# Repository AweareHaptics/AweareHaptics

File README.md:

# AweareHaptics

Nowadays, the french population amounts more than 207 000 blind people and more than a million people suffer from visual defficiencies. According to the OMS, the number of visually impaired people should triple by 2050. Currently, the support tools developed and available for these people are not technologically advanced and often require significant purchase costs. We therefore decided to develop a tool to help with spatial orientation, accessible to all, for the blind or visually impaired.

**Aweare Haptics is an open source project on the development of a haptic vest allowing the blind or visually impaired to orient themselves in their surrounding environment.**

Aweare Haptics is a student project in partnership with the CRI.

This readme is a comprehensive guide on how to use the Git so you can build the vest for yourself. It also contains explainations on our choices so you can adapt it for yourself.

### Requirements

List of hardware required to get started with your project:

- 3D printer
- Soldering station
- Sewing station

# Synopsis

The haptic vest is composed of infrared sensors to detect obstacles, 2 movuinos to transfer instructions to the motor actuators sewn to the vest. The location of the vibrators was determined by performing a sensitivity mapping. 

# Brief

The vest will be entirely made by you. This guide will give you the different components we used to make our own vest. If at any point in the process of building it, you think that something we made isn't adapted for you, don't hesitate to customize it. This repository is mostly a guideline to help you along the way. We will explain our thought process so you can better understand our choices.

The Vest in itself is made in 2 separate parts. Each part is controlled by one movuino board. The first one is the motor control. 

# Architecture of this repository

This repository is divided into multiple folders :

## 3D Model

In this folder you will find two other folders. They include the 3D model that we use to make the vest :

- "Holders" contains the ones used to support the sensors in the vest

- "Caps" contains the ones used to encapsulate the vibration motor.

## Code 

This folder is composed of two folders :
- "Motors" contains the code to upload to the movuino that operates the motors
- "Sensors" contains the code to upload to the movuino that operates the sensors

The code manages the wifi connection. The motor part takes care of setting up the server whereas the sensors represent the hotspot/client.

#  Motor Actuators

## Required hardware

For every motor used you'll need the following components:
- Néomotor PCB: you can find our brd file in the repository
- SMD resistor 10Ω type 0805 : link to [manufacturer reference : CRCW080510R0FKEA](https://fr.rs-online.com/web/p/resistances-cms/6790825/)
- SMD resistor 100Ω type 0805 : link to [manufacturer reference : CR0805-FX-1000ELF](https://fr.rs-online.com/web/p/resistances-cms/7408978/)
- SMD resistor 442Ω type 0805 : link to [manufacturer reference : ERA6AEB4420V](https://fr.rs-online.com/web/p/resistances-cms/7086023/)
- SMD resistor 4KΩ type 0805 : link to [manufacturer reference : CRCW08054K02FKEA](https://fr.rs-online.com/web/p/resistances-cms/6791471/)
- Capacitor type 104 : 10nF, SMD type 0805 :  link to  [manufacturer reference : CC0805KRX7R9BB103](https://fr.rs-online.com/web/p/condensateurs-ceramique-multicouches/4614013/)
- Transitor npn SOT-32 :  link to  [manufacturer reference : MMBT3904LT1G](https://fr.rs-online.com/web/p/transistors-bipolaires-bjt/5450343/)
- Vibration Motor [Type Model NFP-P0716](https://nfpshop.com/product/7mm-vibration-motor-16mm-type-model-nfp-p0716-3v-12000rpm-7-3g-amplitude)

## Setting up the PCB

You'll need to order or make your own PCB with the brd file found on this repository to make the motors work.

## Mounting/Assembly

## Wiring
 - Connect the GND pin of the movuino to the IN GND pin of the pcb
 - Connect the +5V pin of the movuino to the IN +5V pin of the pcb
 - Connect the +3V pin of the movuino to the IN +3V pin of the pcb
 - Connect the D9 pin of the movuino to the IN DIN pin of the pcb
 - Connect the two motor wires to the motor labeled pins on the pcb (in whatever order as the motor isn't polarized)

Then connect :
 - The OUT GND of the first pcb to the following pcb on its IN GND pin
 - The OUT +5V of the first pcb to the following pcb on its IN +5V pin
 - The OUT +3V of the first pcb to the following pcb on its IN +3V pin
 - The DOUT pin of the first pcb to the DIN of the following pcb 

## Code 

Upload the source code to the movuino

The movuino card becomes a sever socket on the address 192.168.4.2
A maximum of one client can connect at a time : this can be changed in the file : ... define BN_CLIENT // TODO ADD NAME OF FILE

The server receives messages from the clients. The messages need to be formated in strings containing the id of the vibration motor that we want to pilot along with its intensity whose value ranges from 0 to 3

## Solder the PCB

The motors PCB are made to all be in series of one another. The first PCB has its 3.3V to the 3 Volts battery. The 5V is connected to the movuino's 5V. Then the DIN is connected to the D4 pin of the movuino. The ground is conected to the shared ground of the movuino and the 3V battery.

For the I/Os of the other PCB, the OUT first board is directly linked to the IN of the second board. The OUT of the second is connected to the IN of the third and continue until all your motor controller are linked. The OUT of the last board doesn't need to be connected anywhere.

For the Motor pins, you just need to connect them to a exentric mass vibration motor. They can be wired in both direction.

For each PCB you also have to solder the resistors, capacitor, transistor and the microcontroller.

### soldering the passive components :

R1 is the 400 Ohms resistor.
R2 is the 4K Ohms resistor.
R3 is the 100 Ohms resistor.
R4 is the 10 Ohms resistor.
C1 is the capacitor.

### soldering the Microcontroller :

To solder the MicroController you have to put the tiny hole such as it is facing you and in the top left. Then you can solder it to the board. 

## Mounting

# Infrared Sensors

## Required hardware

- Prototyping plate : link to [manufacturer reference  : 743635] https://fr.rs-online.com/web/p/cartes-matrices/4853892/
- Infrared sensor VL53L0X TECNOIOT (measures up to 2 meters) : link to [manufacturer reference : A513-VL53L0X-297-5PCS ]
https://www.amazon.fr/TECNOIOT-VL53L0X-Flight-Distance-GY-VL53L0XV2/dp/B084BTP479/ref=sr_1_6?__mk_fr_FR=%C3%85M%C3%85%C5%BD%C3%95%C3%91&crid=6Q645XXPDDA7&dchild=1&keywords=lidar+arduino&qid=1606946373&sprefix=lidar+%2Caps%2C326&sr=8-6
- Infrared sensor VL53L1X STMicroelectronics (measures up to 4 meters): link to [manufacturer reference : VL53L1X-SATEL] https://fr.rs-online.com/web/p/modules-de-developpement-pour-capteurs/1827794/?cm_mmc=FR-PPC-DS3A-_-bing-_-3_FR_FR_Modules+de+d%C3%A9veloppement+pour+capteurs_STMicroelectronics_Exact-_-STMicroelectronics+-+Modules+de+d%C3%A9veloppement+pour+capteurs+-+1827794-_-vl53l1x+satel&matchtype=e&kwd-71743717917902:loc-66&gclid=534000e661d01b55fc8760f1bc5fa77a&gclsrc=3p.ds&msclkid=534000e661d01b55fc8760f1bc5fa77a

## Setting up the prototyping plate

Solder a line for 5V, a line for GND, a line for SCL and a line for SDA.

## Mouting/Assembly

## VLX53L0X pins

### Board description

Take the board with its captor facing you and in the right side of the board. The pins are in the left side. From top to bottom we have :

- Vin 
- Ground
- SCL
- SDA
- GPIO1 (unused for this project)
- XSHUT

## VLX53L1X pins

Schematics for the VL53L1X corresponding pins :

### Schematic description

Take the board with its captor facing you and in the right side of the board. The pins are in the left side. The most bottom left is the INT pin, it is unused for this project. The one above the INT pin is the XSDN pin. Above the XSDN pin is the Vdd pin. Right to Vdd is the ground pin. Below the ground you have the SDA pin. And below SDA is SCL. All other pin are unused.

## Wiring

### Wiring schematic :

### Schematic description

 - Connect the GND pin of the movuino to any line on the prototyping plate which becomes its designated line. (GND)
 - Connect the +3V pin of the movuino to any line on the prototyping plate which becomes its designated line. (+3V)
 - Connect the SCL pin of the movuino to any line on the prototyping plate which becomes its designated line. (SCL)
 - Connect the SDA pin of the movuino to any line on the prototyping plate which becomes its designated line. (SDA)

Connect then for every sensor:

 - Connect the GND pin of the sensor to the desigLnated GND line on the prototyping plate
 - Connect the VIN/VDD pin of the sensor to the designated +3V line on the prototyping plate
 - Connect the SCL pin of the sensor to the designated SCL line on the prototyping plate
 - Connect the SDA pin of the sensor to the designated SDA line on the prototyping plate
 - Connect the pins D3, D4, D5... of the movuino to the XSHUT pin for the sensor VL53L0X or XSDN pin for the VL53L1X sensor.

## Code 

# Sensibility protocole

Sensibility mapping process:

Before getting started with the mapping, you'll need to prepare your work environment.
You'll need to carry out the protocole by using the body proportions of the person wearing the vest.
You'll need to use a vibration motor connected to a power source of 3.3V to map out the sensitive areas of the person's body.

## First step : Divide into squares the person's body

We'll seperate the torso, the back and the arms into different testing areas.

 -On the torso : seperate in 10 different areas
 --Area 1 and 2 : Upper left and right part of the torso 
 --Area 3 and 4 : left and right part of the chest
 --Area 5 and 6 : left and right part of the ribs under the chest area
 --Area 7 and 8 : left and right part of the belly
 --Area 9 and 10 : left and right part of the hips

 -On the back : seperate in 8 different areas.
 --Area 1 and 2 : left and right part of the shoulder blades
 --Area 3 and 4 : left and right part of the ribs under the shoulder blades
 --Area 5 and 6 : left and right part of lower back (lumbar region)
 --Area 7 and 8 : left and right part of hips

 -On the arms : seperate in 4 different areas
 --Area 1 : right shoulder
 --Area 2 : right arm 
 --Area 3 : left shoulder
 --Area 4 : left arm 

## Second step : Mapping out the sensitive areas

- Start by powering up the motor with a voltage of 3.3V.
WARNING : In order for the mapping to be correct, the motor needs to be supplied with a constant voltage of 3.3V for the duration of the tests.

-In order to familiarize yourself with the feeling of the vibrating motor, try out every area at least once before ruling out the ones that are too sensitive.

-Position the motor on every testing area and define one of the following feedback:
--Extremely sensitive area : red
--Sensitive area : orange
--Not very sensitive area : yellow
--Not recommended area (private regions or no sensitivity) : white

-We recommend repeating the protocole multiple times for better results.

# Authors

* [**Guicharnaud Léo**](https://github.com/Lightman31)
* [**Buot Adrien** ](https://github.com/Bubu781 )
* [**terre Mikhali** ](https://github.com/Mikhali)
* [**Sabatey Clara** ](https://github.com/clarasbty)
* [**Noiraux Coline** ](https://github.com/NoireauxColine)
* [**Beurotte Marine** ](https://github.com/mama98)

# Version Francaise :

De nos jours, on compte parmis la population française plus de 207 000 aveugles et plus d’1 million de personnes souffrant de cécité visuelle. De plus, d’après l’OMS, le nombre de malvoyants pourrait trippler d’ici 2050. Actuellement, les outils d’aide développés pour ces personnes sont peu avancés technologiquement et nécessite souvent d’important coût d’achat. Nous avons donc décidé de développer un outil d’aide à l’orientation dans l’espace accessible à tous pour les personnes aveugles et malvoyantes.

**Aweare Haptics est une veste haptique open source permettant aux personnes aveugles et malvoyantes de s’orienter dans leur environnement.**

# Pour commencer

Entrez ici les instructions pour bien débuter avec votre projet...

### Pré-requis

Ce qu'il est requis pour commencer avec votre projet du point de vue du matériel

- Imprimante 3D
- Poste de soudure
- Poste de couture

# Démarrage

Notre veste sera composée de capteurs infrarouge pour détecter la présence d’obstacle et de movuino pour transmettre l’information aux actuateurs présent sur la veste. L’emplacement des vibreurs a été déterminés par la réalisation d’une cartographie de sensibilité.

#  Partie moteurs actuateurs

## Matériel

Pour chaque moteur vous aurez besoin de :

- faire faire un pcb néomotor : le fichier brd est dans le repo
- résistance 10Ω boitier 0805 : lien vers la [référence fabriquant : CRCW080510R0FKEA](https://fr.rs-online.com/web/p/resistances-cms/6790825/)
- résistance 100Ω boitier 0805 : lien vers la [référence fabriquant : CR0805-FX-1000ELF](https://fr.rs-online.com/web/p/resistances-cms/7408978/)
- résistance 442Ω boitier 0805 : lien vers la [référence fabriquant : ERA6AEB4420V](https://fr.rs-online.com/web/p/resistances-cms/7086023/)
- résistance 4KΩ boitier 0805 : lien vers la [référence fabriquant : CRCW08054K02FKEA](https://fr.rs-online.com/web/p/resistances-cms/6791471/)
- Condensateur type 104 : 10nF, boitier 0805 : lien vers la [référence fabriquant : CC0805KRX7R9BB103](https://fr.rs-online.com/web/p/condensateurs-ceramique-multicouches/4614013/)
- transitor npn simple boitier SOT-32 : lien vers la [référence fabriquant : MMBT3904LT1G](https://fr.rs-online.com/web/p/transistors-bipolaires-bjt/5450343/)
- moteur vibrant [Type Model NFP-P0716](https://nfpshop.com/product/7mm-vibration-motor-16mm-type-model-nfp-p0716-3v-12000rpm-7-3g-amplitude)

## Fabrication du pcb

vous aurez besoin de commander ou bien de fabriquer des PCB, pour bien faire fonctionner les moteurs vibrant

## Montage

AJOUTER SCHEMA

## Branchements
 - brancher le GND de la movuino sur le GND du pcb
 - brancher le +5V de la movuino sur le +5V du pcb
 - brancher le +3V de la movuino sur le +3V du pcb
 - brancher la pin D9 de la movuino sur le DIN du pcb
 - brancher les deux fils sur moteur sur le bornes moteur du pcb. (le moteur n'est pas polarisé)

brancher ensuite :
 - le GND du pcb sur le GND du pcb suivant
 - le +5V de pcb sur le +5V du pcb suivant
 - le +3V de pcb sur le +3V du pcb suivant
 - la pin D9 de pcb sur le DIN du pcb suivant

## Code 

téléverser le code source sur la movuino

la carte movuino devient un serveur socket sur l'adresse 192.168.4.2
1 client max peut s'y connecter : ce nombre est modifiable dans le fichier ... : le define BN_CLIENT // TODO : dire le nom du fichier  

le serveur ne fait que recevoir des messages des clients. le message doit etre formaté un string cntenant le numéo de l'actuateur à faire vibrer, ainsi qu'une intensité ayant une valeur comprise entre 0 et 3 

## Souder les PCBd

## Monter..

#  Partie capteurs infrarouge

## Matériel

- Plaque de prototypage : lien vers la [référence fabriquant : 743635] https://fr.rs-online.com/web/p/cartes-matrices/4853892/
- Capteur infrarouge VL53L0X TECNOIOT (mesure jusqu'à 2m) : lien vers la [référence fabriquant : A513-VL53L0X-297-5PCS ]
https://www.amazon.fr/TECNOIOT-VL53L0X-Flight-Distance-GY-VL53L0XV2/dp/B084BTP479/ref=sr_1_6?__mk_fr_FR=%C3%85M%C3%85%C5%BD%C3%95%C3%91&crid=6Q645XXPDDA7&dchild=1&keywords=lidar+arduino&qid=1606946373&sprefix=lidar+%2Caps%2C326&sr=8-6
- Capteur infrarouge VL53L1X STMicroelectronics (mesure jusqu'à 4m): lien vers la [référence fabriquant : VL53L1X-SATEL] https://fr.rs-online.com/web/p/modules-de-developpement-pour-capteurs/1827794/?cm_mmc=FR-PPC-DS3A-_-bing-_-3_FR_FR_Modules+de+d%C3%A9veloppement+pour+capteurs_STMicroelectronics_Exact-_-STMicroelectronics+-+Modules+de+d%C3%A9veloppement+pour+capteurs+-+1827794-_-vl53l1x+satel&matchtype=e&kwd-71743717917902:loc-66&gclid=534000e661d01b55fc8760f1bc5fa77a&gclsrc=3p.ds&msclkid=534000e661d01b55fc8760f1bc5fa77a

## Elaboration de la plaque de prototypage 

METTRE PHOTO DE LA PLAQUE

faire une ligne 5V, une ligne GND, une ligne SCL et une ligne SDA

## Montage

Schema des pins du VL53L1X :

## Branchements

 - brancher le GND de la movuino sur une ligne de la plaque 
 - brancher le +3V de la movuino sur une ligne de la plaque 
 - brancher la pin SCL de la movuino sur une ligne de la plaque
 - brancher la pin SDA de la movuino sur une ligne de la plaque

brancher ensuite pour chaque capteurs :

 - brancher la pin GND du capteur a la ligne GND de la plaque
 - brancher la pin VIN/VDD du capteur a la ligne 3V de la plaque
 - brancher la pin SCL du capteur a la ligne SCL de la plaque
 - brancher la pin SDA du capteur a la ligne SDA de la plaque
 - brancher la pin D3, D4, D5... de la movuino sur le XSHUT des capteurs VL53L0X ou XSDN pour les capteurs VL53L1X.

## Code 

# Protocole de sensibilité

Processus de réalisation de la cartographie:

Avant de commencer la cartographie, il faut préparer l'environnement de travail.
Ce protocole est à réaliser sur le corps de la personne qui portera la veste.
Pour réaliser ce protocole, il faut se munir d'un moteur vibrant branché à une puissance de 3,3V.

## Première étape : Qadriller le corps de la personne 

Nous allons séparer le buste, le dos et les bras en différentes zones à tester.

-Sur le devant du corps : séparer en 10 zones.
--Zone 1 et 2 : Haut du buste partie droite et partie gauche
--Zone 3 et 4 : Poitrine partie droite et partie gauche
--Zone 5 et 6 : Cotes sous poitrine partie droite et partie gauche
--Zone 7 et 8 : Ventre partie droite et partie gauche
--Zone 9 et 10 : Hanches partie droite et partie gauche

-Sur le derrière du corps : séparer en 8 zones.
--Zone 1 et 2 : Omoplates partie droite et partie gauche
--Zone 3 et 4 : Cotes sous omoplates partie droite et partie gauche
--Zone 5 et 6 : Bas du dos (zone lombaire) partie droite et partie gauche
--Zone 7 et 8 : Hanches partie droite et partie gauche

-Sur les bras : séparer en 4 zones 
--Zone 1 : bras droit épaule
--Zone 2 : bras droit haut du bras
--Zone 3 : bras gauche épaule
--Zone 4 : bras gauche haut du bras

## Deuxième étape : Elaboration de la cartographie

-Commencer par allumer le moteur avec une puissance de fonctionnement de 3,3V.
ATTENTION : Pour que la cartographie soit efficace, le moteur doit rester à 3,3V pendant tout le test.

-Passer une première fois le moteur sur l'ensemble des zones pour se familiariser avec le ressenti des vibrations.

-Positionner ensuite le moteur sur chaque zone à tester et définir un ressenti prédéfini:
--Zone fortement sensible : Zone Rouge
--Zone sensible : Zone Orange
--Zone peu sensibe : Zone Jaune
--Zone déconseillée (mauvais placement ou aucune sensibilité) : Zone Blanc

-Nous vous conseillons de le faire plusieurs fois pour des résultats adaptés.

# Auteurs

* [**Guicharnaud Léo**](https://github.com/Lightman31)
* [**Buot Adrien** ](https://github.com/Bubu781 )
* [**terre Mikhali** ](https://github.com/Mikhali)
* [**Sabatey Clara** ](https://github.com/clarasbty)
* [**Noiraux Coline** ](https://github.com/NoireauxColine)
* [**Beurotte Marine** ](https://github.com/mama98)

## Versions 
Liste des versions : [**Cliquer pour afficher les tags**](https://github.com/AweareHaptics/AweareHaptics/tags)

## Fabriqué avec

- [Arduino](https://www.arduino.cc/) - IDE
- [VScode](https://code.visualstudio.com/) + [PlatformIO](https://platformio.org/) - éditeur de texte et IDE
- [Fusion360](https://www.autodesk.fr/products/fusion-360/overview) - logiciel de modélisation 3D 
- [Eagle](https://www.autodesk.fr/products/eagle/overview) - logiciel de conception électronique

## License
Ce projet est sous licence ``exemple: WTFTPL`` - voir le fichier [LICENSE.md](LICENSE.md) pour plus d'informations

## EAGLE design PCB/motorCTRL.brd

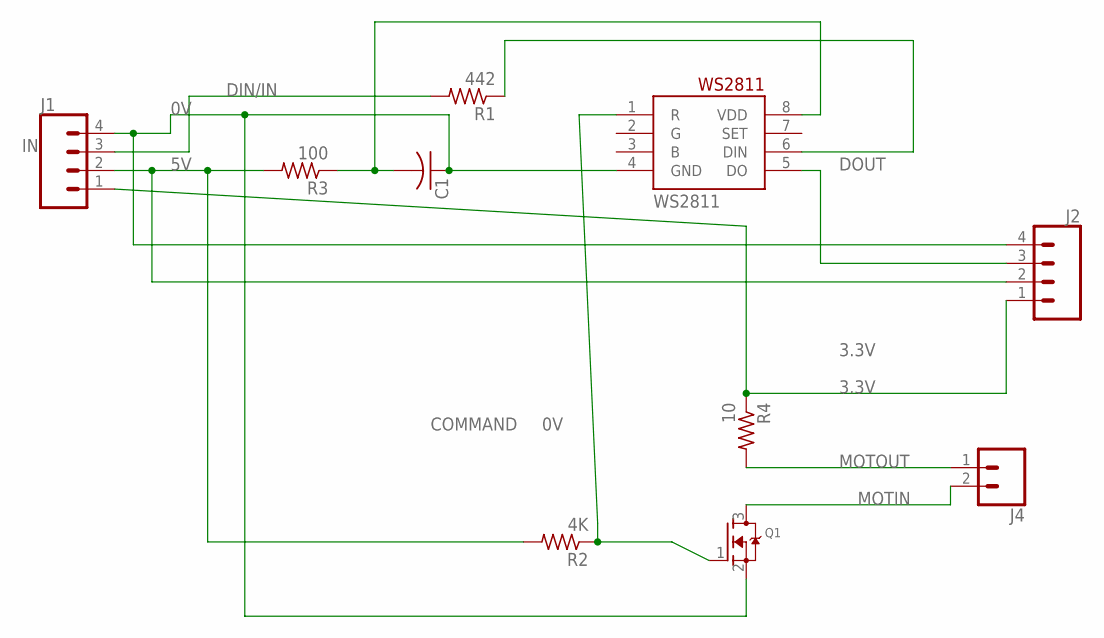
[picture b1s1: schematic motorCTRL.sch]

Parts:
C1: C-USC0805; C0805
J1, J2: CONN_04; 1X04
J4: CONN_02; 1X02
Q1: MOSFET-NREFLOW; SOT23
R1: 442; R0805
R2: 4K; R0805
R3: 100; R0805
R4: 10; R0805
WS2811: WS2811-SOP8; SO08-SKINNYPADS

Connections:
0V: C1.1, J1.4, J2.4, Q1.2 (S), WS2811.4 (GND)
3.3V: J1.1, J2.1, R4.1
5V: J1.2, J2.2, R2.2, R3.2
COMMAND: Q1.1 (G), R2.1, WS2811.1 (R)
DIN/IN: J1.3, R1.2
DOUT: J2.3, WS2811.5 (DO)
MOTIN: J4.2, Q1.3 (D)
MOTOUT: J4.1, R4.2
unnamed: R1.1, WS2811.6 (DIN)
VCC: C1.2, R3.1, WS2811.8 (VDD)

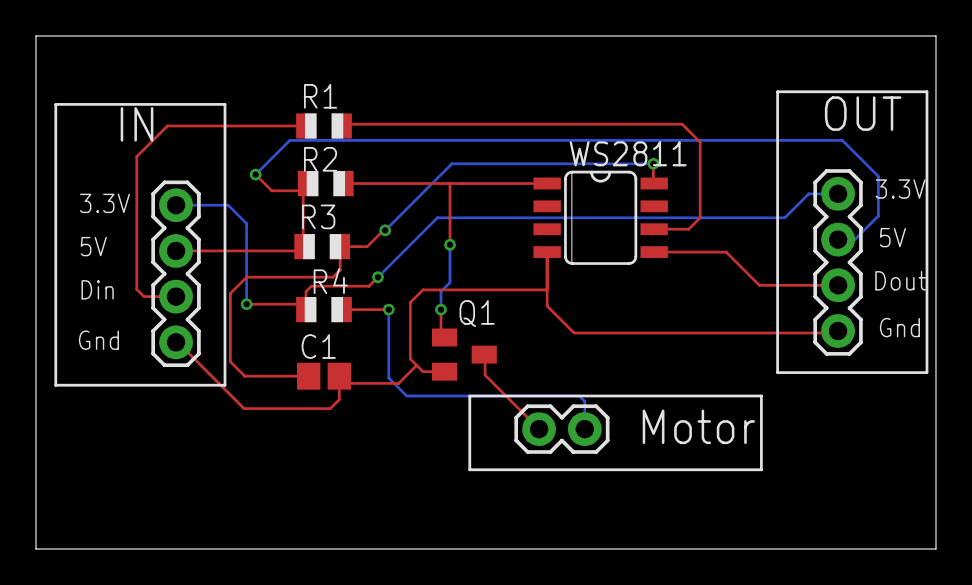
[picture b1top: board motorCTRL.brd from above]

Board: 2 copper layers, 50.0 x 28.5 mm, 10 parts (0 on the bottom side), 10 nets.

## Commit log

2021-01-05 Added gitignore
2021-01-05 premier test
2021-01-05 test2
2021-01-05 mini correc
2021-01-05 add members
2021-01-20 Create CNAME
2021-01-20 Update CNAME
2021-01-20 code for the actuators
2021-01-21 premier jet des modeles
2021-01-21 premier jet composants
2021-01-21 ajout des références fabriquant
2021-01-21 composants OK
2021-01-21 reamdme
2021-01-21 correction du nom du projet
2021-01-21 added the code of the server/sensors
2021-01-21 auteurs OK
2021-01-21 Added the child classes for the futures sensors
2021-01-22 Correction
2021-01-25 verification de l'outil team
2021-01-25 changed client to server
2021-01-25 test outil team
2021-01-25 tiny change
2021-01-25 erased errors
2021-01-25 Added long distance sensors
2021-01-27 images branchement + update readme.md
2021-01-28 changed server to client
2021-01-29 readme.md
2021-01-29 modified actuators
2021-01-31 Fixed the long range sensor idle state
2021-01-31 Add comments for SensorLong class
2021-02-01 revert client
2021-02-01 rename
2021-02-01 Add instructions for the long sensors
2021-02-01 Add VL53L1X pin schematics
2021-02-01 documentation
2021-02-01 uncomplete translation from fr to en
2021-02-01 fixes
2021-02-01 Add english version of the readme
2021-02-01 Fix VL53L1X image not showing
2021-02-02 Add code for working prototype
2021-02-02 working actuator code for prototype
2021-02-02 update final presentation
2021-02-02 fixed images
2021-02-11 modèles 3D + brd et sch du PCB

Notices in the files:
README.md:
License:
Ce projet est sous licence ``exemple: WTFTPL`` - voir le fichier [LICENSE.md](LICENSE.md) pour plus d'informations
parts and their libraries:
SparkFun-Connectors: Licensing: Creative Commons ShareAlike 4.0 International - https://creativecommons.org/licenses/by-sa/4.0
